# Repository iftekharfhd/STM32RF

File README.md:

# STM32RF
A STM32 microcontroller module capable of programming and RX/TX signals

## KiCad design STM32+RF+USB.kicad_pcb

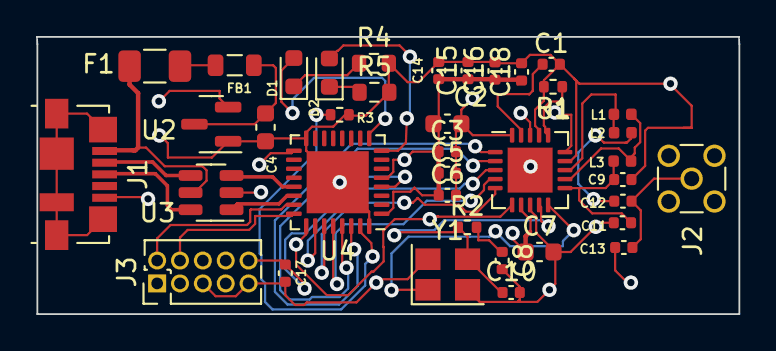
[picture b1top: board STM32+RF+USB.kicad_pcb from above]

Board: 4 copper layers, 39.0 x 15.4 mm, 38 parts (0 on the bottom side), 32 nets.

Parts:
C1: 33n; C_0402_1005Metric
C2, C4, C7: 10u; C_0603_1608Metric
C3, C5, C6: 10n; C_0402_1005Metric
C8, C10: 12p; C_0402_1005Metric
C9: 2n2; C_0402_1005Metric
C11: 4p7; C_0402_1005Metric
C12: 1p5; C_0402_1005Metric
C13: 1p; C_0402_1005Metric
C14: 1u; C_0402_1005Metric
C15, C16, C17, C18: 100n; C_0402_1005Metric
D1: GR; LED_0603_1608Metric
D2: YE; LED_0603_1608Metric
F1: 100mA; Fuse_1206_3216Metric
FB1: 100 @ 100MHz; L_0805_2012Metric
J1: USB_B_Micro; USB_Micro-B_Molex_47346-0001
J2: SMA; MMCX_Molex_73415-1471_Vertical
J3: ARM 10pin; PinHeader_2x05_P1.27mm_Vertical
L1: 8n2; L_0402_1005Metric
L2: 3n9; L_0402_1005Metric
L3: 2n7; L_0402_1005Metric
R1: 22k; R_0402_1005Metric
R2: 1M; R_0402_1005Metric
R3: 10k; R_0402_1005Metric
R4, R5: 2k2; R_0603_1608Metric
U1: nRF24L01P; QFN-20-1EP_4x4mm_P0.5mm_EP2.5x2.5mm
U2: XC6206P332MR; SOT-23
U3: USBLC6-2SC6; SOT-23-6
U4: STM32L432KBU6; QFN-32-1EP_5x5mm_P0.5mm_EP3.45x3.45mm
Y1: 16MHz; Crystal_SMD_3225-4Pin_3.2x2.5mm

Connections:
+3V3: C2.1, C3.1, C5.1, C6.1, C7.1, C14.1, C15.1, C16.1, C18.1, J3.1, U1.7 (VDD), U1.15 (VDD), U1.18 (VDD), U2.2 (VO), U4.1 (VDD), U4.5 (VDDA), U4.17 (VDD)
+5V: F1.2, J1.1 (VBUS), U3.5 (VBUS)
GND: C1.2, C2.2, C3.2, C4.2, C5.2, C6.2, C7.2, C8.2, C9.1, C10.2, C11.1, C13.1, C14.2, C15.2, C16.2, C17.2, C18.2, J1.5 (GND), J2.2 (Ext), J3.3, J3.5, J3.9, R1.2, R3.2, R4.2, R5.2, U1.8 (VSS), U1.14 (VSS), U1.17 (VSS), U1.20 (VSS), U2.1 (GND), U3.2 (GND), U4.16 (VSS), U4.32 (VSS), U4.33 (VSS), Y1.2, Y1.4
NRF_ANT1: L1.2, L3.2, U1.12 (ANT1)
NRF_ANT2: L1.1, L2.1, U1.13 (ANT2)
NRF_CE: U1.1 (CE), U4.30 (PB7)
NRF_IRQ: U1.6 (IRQ), U4.25 (PA15)
NRF_VDD_PA: C9.2, C11.2, L3.1, U1.11 (VDD_PA)
NRF_XC1: C8.1, R2.2, U1.10 (XC1), Y1.1
NRF_XC2: C10.1, R2.1, U1.9 (XC2), Y1.3
NRST: C17.1, J3.10, U4.4 (NRST)
unnamed: C12.2, L2.2
unnamed: D1.2 (A), U4.9 (PA3)
unnamed: D1.1 (K), R4.1
unnamed: D2.2 (A), U4.8 (PA2)
unnamed: D2.1 (K), R5.1
unnamed: F1.1, FB1.2
unnamed: C12.1, C13.2, J2.1 (In)
unnamed: C1.1, U1.19 (DVDD)
unnamed: R1.1, U1.16 (IREF)
unnamed: C4.1, FB1.1, U2.3 (VI)
unnamed: R3.1, U4.31 (PH3)
SPI3_!CS: U1.2 (CSN), U4.29 (PB6)
SPI3_MISO: U1.5 (MISO), U4.27 (PB4)
SPI3_MOSI: U1.4 (MOSI), U4.28 (PB5)
SPI3_SCK: U1.3 (SCK), U4.26 (PB3)
SWCLK: J3.4, U4.24 (PA14)
SWDIO: J3.2, U4.23 (PA13)
USB_CONN_D+: J1.3 (D+), U3.6 (IO1)
USB_CONN_D-: J1.2 (D-), U3.4 (IO2)
USB_D+: U3.1 (IO1), U4.22 (PA12)
USB_D-: U3.3 (IO2), U4.21 (PA11)
